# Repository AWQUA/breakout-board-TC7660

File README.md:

# module-dual-supply

### This awesome little board handles a question that persistently pops up in forums: given a voltage and ground (aka a single supply), how can you get a negative voltage (aka a dual supply)? The centerpiece of this board is the awesome little TC7660 inverting DC-DC charge pump, which can easily be sourced for less than $1 in single quantities.

### This module is essentially just a breakout board for the TC7660. There are a couple of things to note when using this chip, and hence this module:

### 1. The positive voltage (V+) must be between 1.5V and 10V. If you need to handle higher voltages, the pin-equivalent TC7662 goes up to 15V but costs a little more than twice as much as the TC7660.

### 2. If, and only if, V+ is less than 3.5V then the header pin pair JP (upper-right of board layout) must be jumpered.

### 3. The capacitors should be 10uF. If you are using polarized capacitors, be very very sure to get the orientations correct.

### 4. As far as we know, the decoupling capacitor C3 is optional for the TC7660; a 2.2uF decoupling capacitor is required for the TC7662 if the input voltage has a large impedance.

### 5. Both the TC7660 and TC7662 can source up to 20mA, which is more than sufficient for running some dual-supply op amps on a single supply board.

### 6. Finally, note that the TC7660H is also available (roughly 20% for expensive than the TC7660) which has a higher switching frequency and only requires 1uF capacitors instead of 10uF capacitors.

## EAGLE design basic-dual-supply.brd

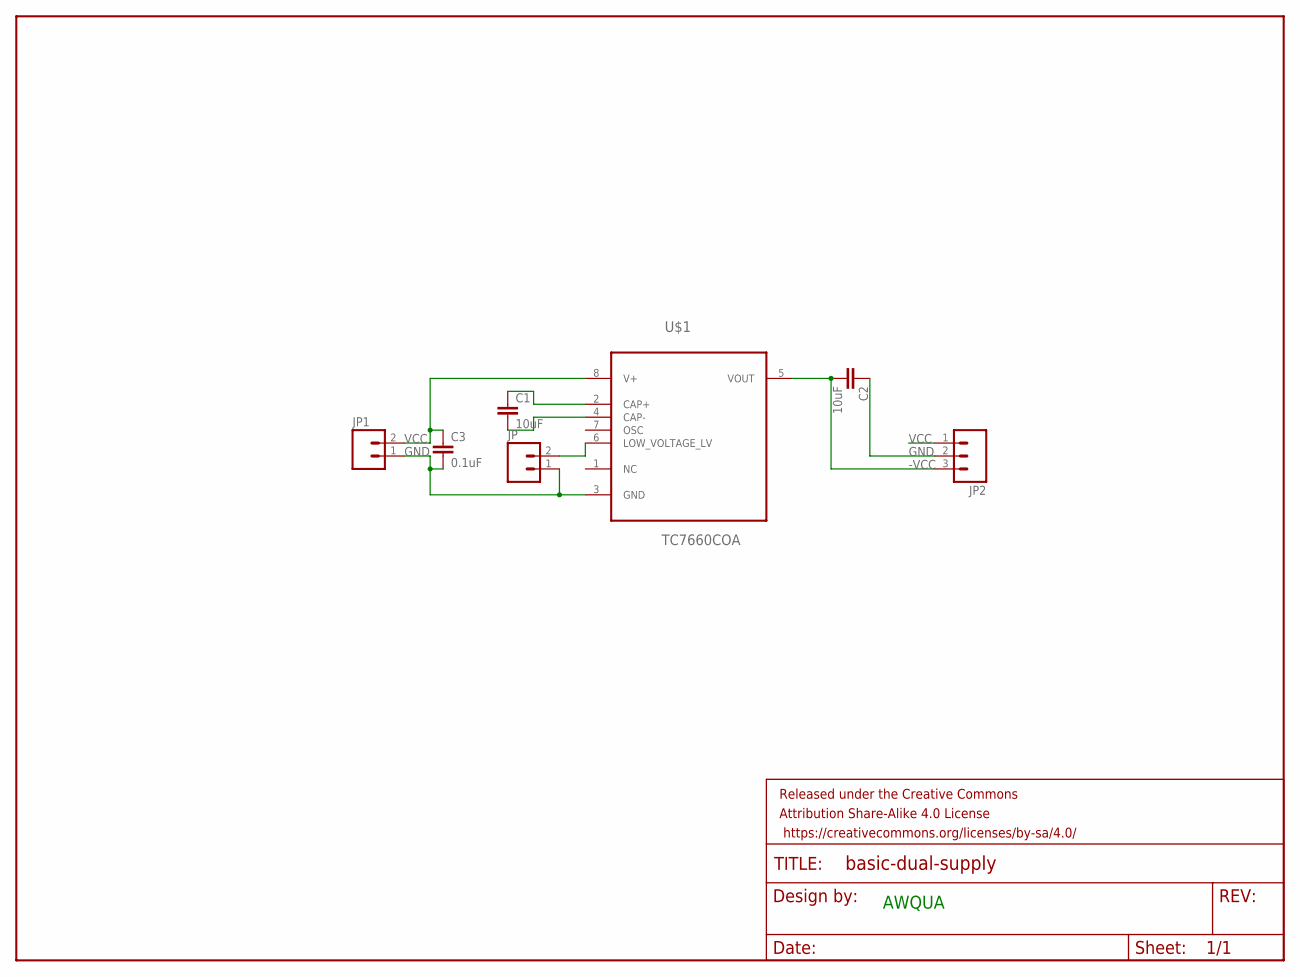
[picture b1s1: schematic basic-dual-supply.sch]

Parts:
C1, C2: 10uF; 0603-CAP
C3: 0.1uF; 0603-CAP
FRAME1: FRAME-LETTER; CREATIVE_COMMONS
JP, JP1: M02PTH; 1X02
JP2: M03PTH; 1X03
U$1: TC7660COA; SOIC127P600X175-8N

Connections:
-VCC: C2.2, JP2.3, U$1.5 (VOUT)
GND: C2.1, C3.2, JP.1, JP1.1, JP2.2, U$1.3 (GND)
unnamed: C1.1, U$1.2 (CAP+)
unnamed: C1.2, U$1.4 (CAP-)
unnamed: JP.2, U$1.6 (LOW_VOLTAGE_LV)
VCC: C3.1, JP1.2, JP2.1, U$1.8 (V+)

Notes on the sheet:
AWQUA

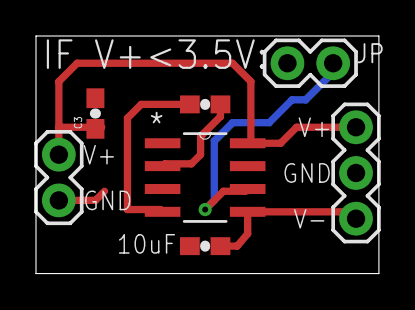
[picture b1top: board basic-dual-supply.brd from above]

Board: 2 copper layers, 19.1 x 13.2 mm, 8 parts (0 on the bottom side), 6 nets.

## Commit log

2017-09-21 initial push

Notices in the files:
parts and their libraries:
SparkFun-Aesthetics: Licensing: Creative Commons ShareAlike 4.0 International - https://creativecommons.org/licenses/by-sa/4.0
SparkFun-Aesthetics: Released under the Creative Commons
Attribution Share-Alike 4.0 License
SparkFun-Aesthetics: (https://creativecommons.org/licenses/by-sa/4.0/)
